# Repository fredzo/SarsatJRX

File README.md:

# Sarsat JRX
Cospas/Sarsat 406MHz beacon decoder based on an ESP32 module.
This project was inspired by the work of F4GMU and F1LVT.

Field use during a SATER exerciser with Ardrasec 31 :

# Hardware
Input stage is based on F1LVT's "deriv-audio" board : http://www.f1lvt.com/files/346-DerivAudio-P3.90.pdf

Second stage is F1LVT's signal shaping stage from DECTRA decoder : http://www.f1lvt.com/files/333E-ConstructionDECTRA2274-P1-English.67.pdf

Audio signal can be provided by either the audio ouput of a receiver (in my case a FT3D portable) or from a NiceRF SA818-S UHF module.

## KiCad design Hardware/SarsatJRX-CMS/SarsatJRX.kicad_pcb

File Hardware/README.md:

# Hardware

The board used is an LilyGo LilyPi : https://opencircuit.fr/produit/lilygo-lily-pi-esp32-wifi-bluetooth-3.5-inch
Based on an ESP32-Wrover-E module from Espressif.

Input stage is based on F1LVT's "deriv-audio" board : http://www.f1lvt.com/files/346-DerivAudio-P3.90.pdf
Second stage is F1LVT's signal shaping stage from DECTRA decoder : http://www.f1lvt.com/files/333E-ConstructionDECTRA2274-P1-English.67.pdf

Audio signal can be provided by either the audio ouput of a receiver or from a NiceRF SA818-S UHF module.

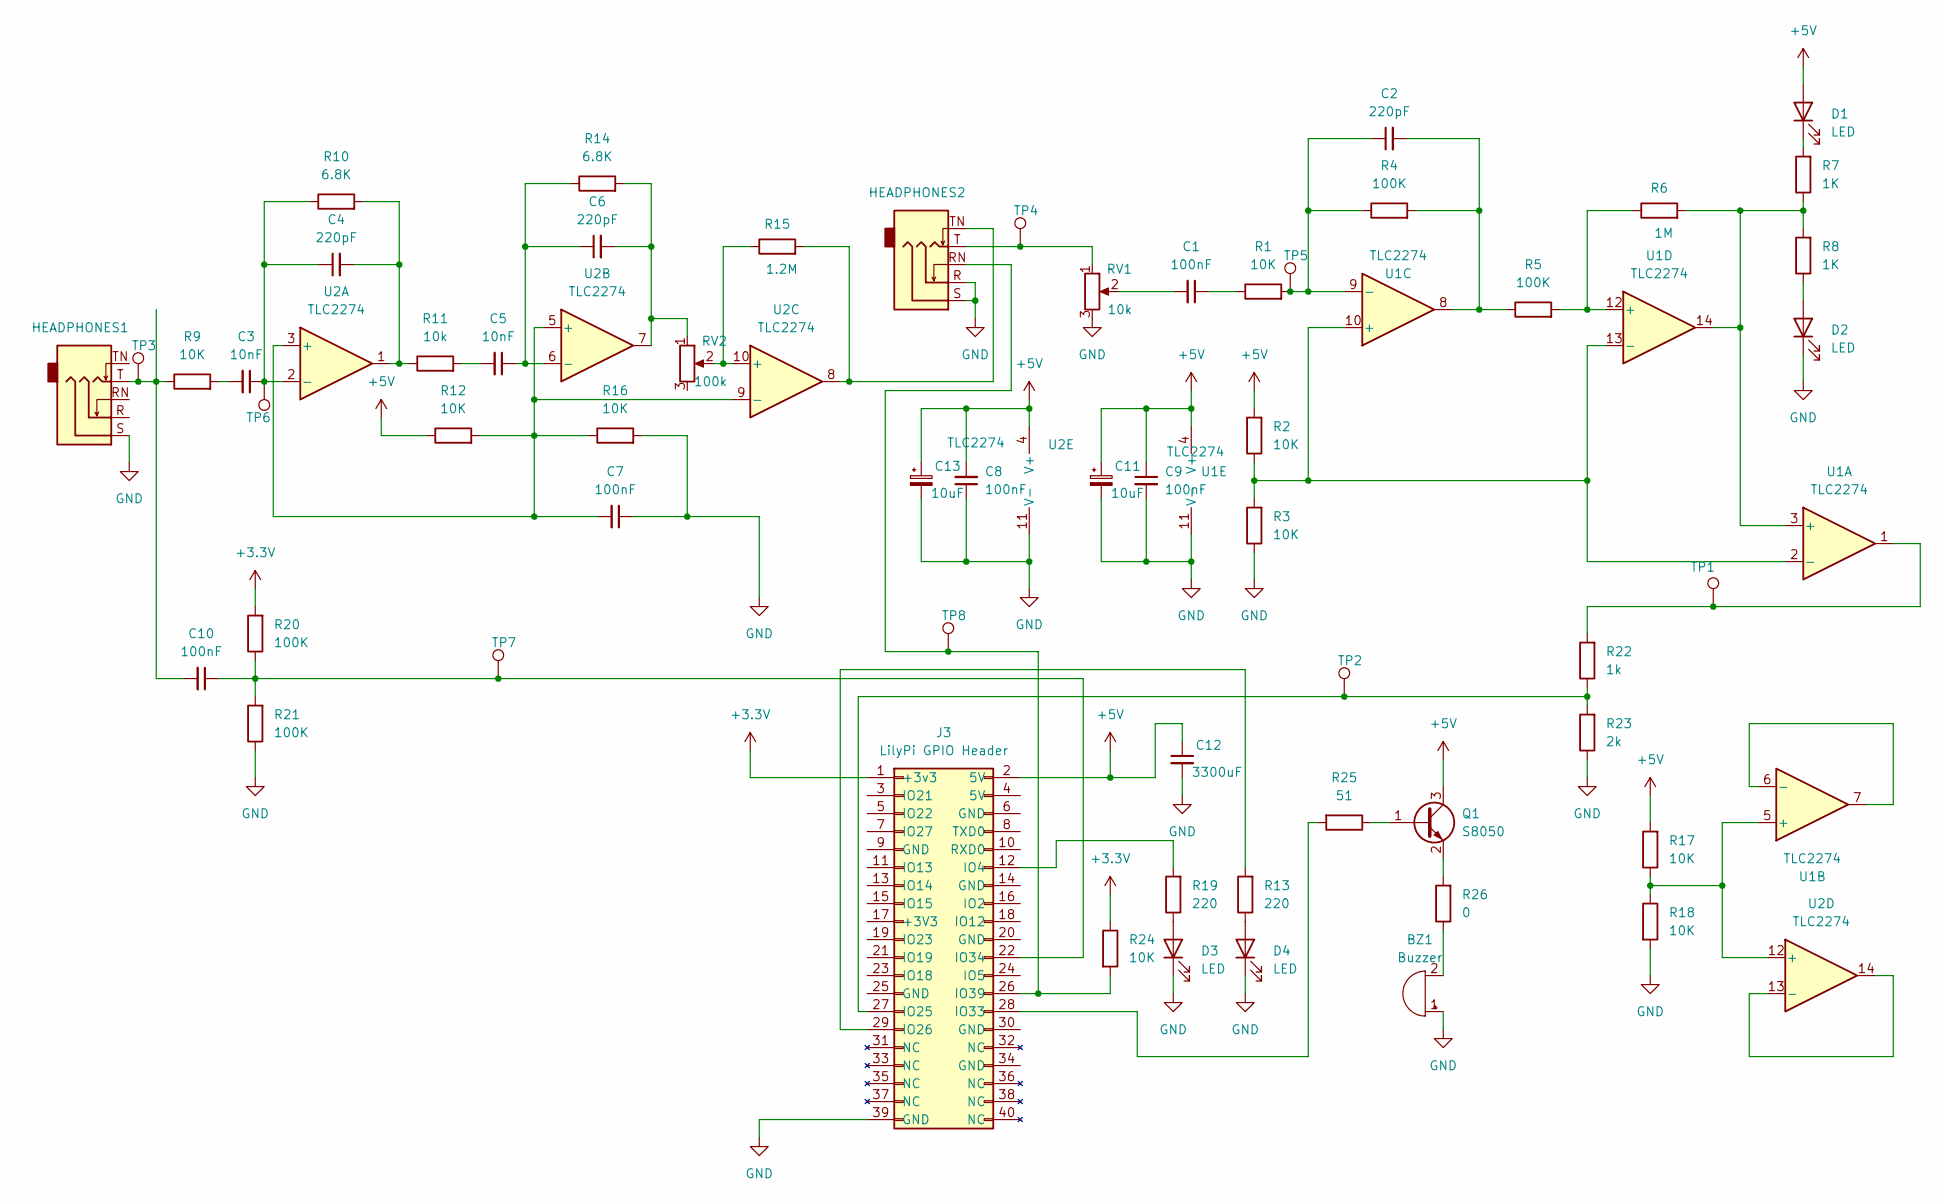
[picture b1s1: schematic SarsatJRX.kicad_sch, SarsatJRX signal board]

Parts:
BZ1: Buzzer; MagneticBuzzer_PUI_AT-0927-TT-6-R-side-horn
C1, C7, C8, C9, C10: 100nF; C_0603_1608Metric
C2, C4, C6: 220pF; C_0603_1608Metric
C3, C5: 10nF; C_0603_1608Metric
C11, C13: 10uF; CP_EIA-3216-18_Kemet-A
C12: 3300uF; CP_Radial_D8.0mm_P3.50mm
D1, D2, D3, D4: LED; LED_D5.0mm
HEADPHONES1, HEADPHONES2: AudioJack3_SwitchTR; PJ-307
J3: LilyPi GPIO Header; RPI_Hat_B+
Q1: S8050; SOT-23-3_L3.0-W1.7-P0.95-LS2.9-BR
R1, R2, R3, R9, R12, R16, R17, R18, R24: 10K; R_0603_1608Metric
R4, R5, R20, R21: 100K; R_0603_1608Metric
R6: 1M; R_0603_1608Metric
R7, R8: 1K; R_0603_1608Metric
R10, R14: 6.8K; R_0603_1608Metric
R11: 10k; R_0603_1608Metric
R13, R19: 220; R_0603_1608Metric
R15: 1.2M; R_0603_1608Metric
R22: 1k; R_0603_1608Metric
R23: 2k; R_0603_1608Metric
R25: 51; R_0603_1608Metric
R26: 0; R_0603_1608Metric
RV1: 10k; Potentiometer_Bourns_3296W_Vertical
RV2: 100k; Potentiometer_Bourns_3296W_Vertical
TP1, TP2, TP3, TP4, TP5, TP6, TP7, TP8: TestPoint_Pad_D1.0mm
U1, U2: TLC2274; SOIC-14_3.9x8.7mm_P1.27mm

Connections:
+3.3V: J3.1 (+3v3), R20.2, R24.1
+5V: C8.2, C9.1, C11.1, C12.1, C13.1, D1.2 (A), J3.2 (5V), Q1.3 (C), R2.2, R12.1, R17.2, U1.4 (V+), U2.4 (V+)
GND: BZ1.1 (+), C7.1, C8.1, C9.2, C11.2, C12.2, C13.2, D2.1 (K), D3.1 (K), D4.1 (K), HEADPHONES1.S, HEADPHONES2.R, HEADPHONES2.S, J3.39 (GND), R3.1, R16.2, R18.2, R21.1, R23.1, RV1.3, U1.11 (V-), U2.11 (V-)
unnamed: BZ1.2 (-), R26.1
unnamed: C1.1, R1.1
unnamed: C1.2, RV1.2
unnamed: C2.2, R4.2, R5.1, U1.8
unnamed: C3.2, R9.2
unnamed: C4.2, R10.2, R11.1, U2.1
unnamed: C5.2, R11.2
unnamed: C6.2, R14.2, RV2.1, U2.7
unnamed: C10.2, HEADPHONES1.T, R9.1, TP3.1
unnamed: D1.1 (K), R7.2
unnamed: D2.2 (A), R8.1
unnamed: D3.2 (A), R19.1
unnamed: D4.2 (A), R13.1
unnamed: HEADPHONES2.T, RV1.1, TP4.1
unnamed: HEADPHONES2.TN, R15.2, U2.8
unnamed: J3.12 (IO4), R19.2
unnamed: J3.27 (IO25), R22.1, R23.2, TP2.1
unnamed: J3.29 (IO26), R13.2
unnamed: J3.28 (IO33), R25.2
unnamed: C10.1, J3.22 (IO34), R20.1, R21.2, TP7.1
unnamed: HEADPHONES2.RN, J3.26 (IO39), R24.2, TP8.1
unnamed: Q1.1 (B), R25.1
unnamed: Q1.2 (E), R26.2
unnamed: R22.2, TP1.1, U1.1
unnamed: R6.2, R7.1, R8.2, U1.3 (+), U1.14
unnamed: R2.1, R3.2, U1.2 (-), U1.10 (+), U1.13 (-)
unnamed: R17.1, R18.1, U1.5 (+), U2.12 (+)
unnamed: U1.6 (-), U1.7
unnamed: C2.1, R1.2, R4.1, TP5.1, U1.9 (-)
unnamed: R5.2, R6.1, U1.12 (+)
unnamed: C7.2, R12.2, R16.1, U2.3 (+), U2.5 (+), U2.9 (-)
unnamed: C3.1, C4.1, R10.1, TP6.1, U2.2 (-)
unnamed: C5.1, C6.1, R14.1, U2.6 (-)
unnamed: R15.1, RV2.2, U2.10 (+)
unnamed: U2.13 (-), U2.14

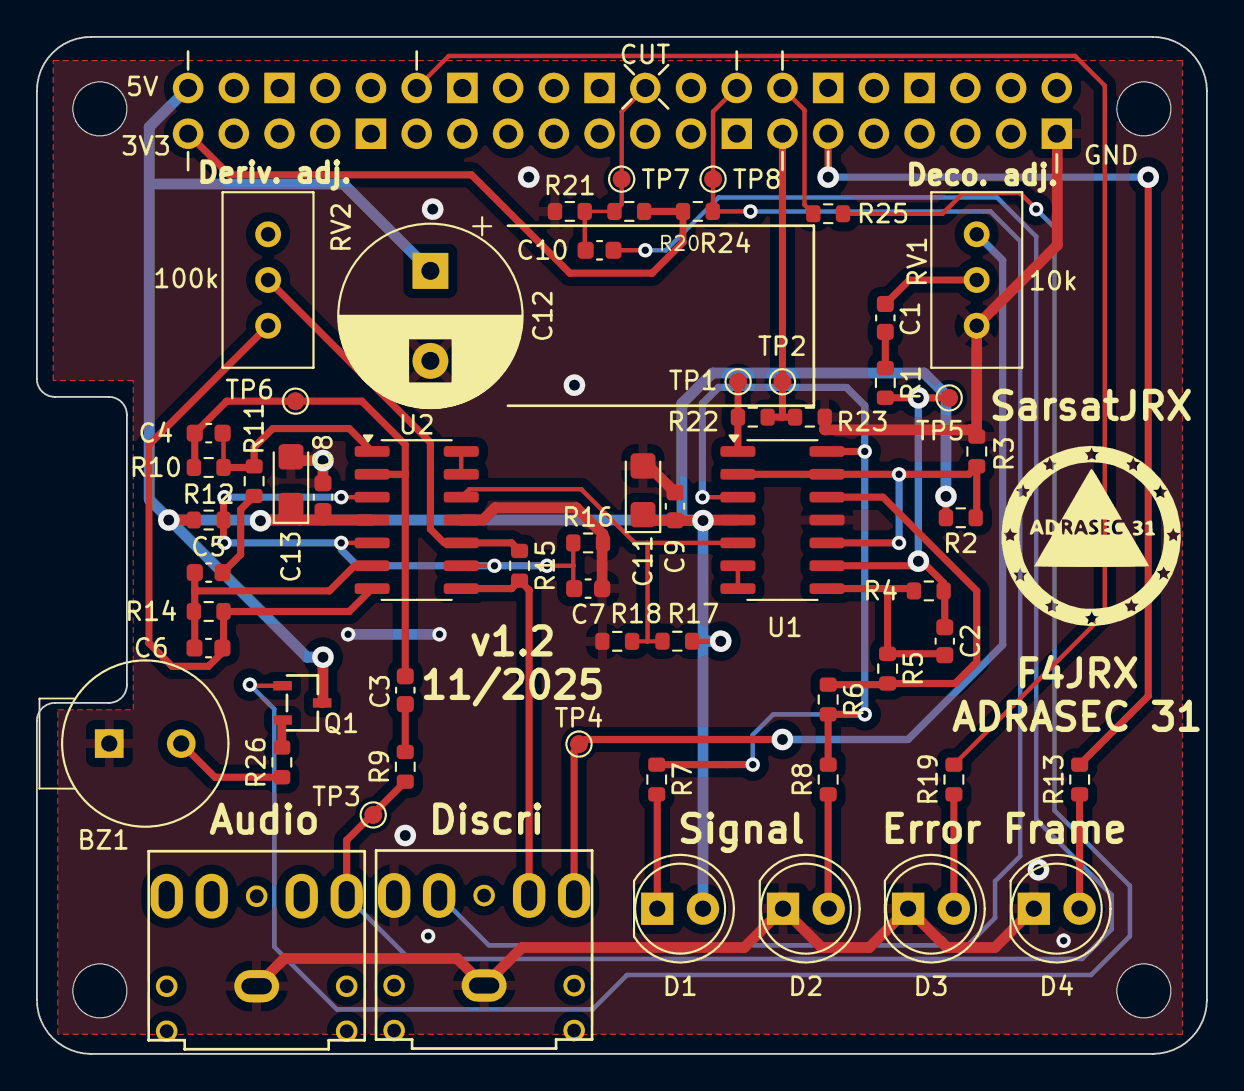
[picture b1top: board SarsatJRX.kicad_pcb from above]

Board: 2 copper layers, 65.0 x 56.5 mm, 60 parts (0 on the bottom side), 38 nets.

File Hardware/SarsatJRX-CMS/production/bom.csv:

Designator,Footprint,Quantity,Value,LCSC Part #
BZ1,MagneticBuzzer_PUI_AT-0927-TT-6-R-side-horn,1,Buzzer,
"C1, C10, C7, C8, C9",0603,5,100nF,
C11,CP_EIA-3216-18_Kemet-A,1,10uF,
C12,CP_Radial_D8.0mm_P3.50mm,1,470uF,
"C2, C4, C6",0603,3,220pF,
"C3, C5",0603,2,10nF,
"D1, D2, D3, D4",LED_D5.0mm,4,LED,
"HEADPHONES1, HEADPHONES2",PJ-307,2,AudioJack3_SwitchTR,
J3,RPI_Hat_B+,1,LilyPi GPIO Header,
Q1,SOT-23-3_L3.0-W1.7-P0.95-LS2.9-BR,1,S8050,
"R1, R11, R12, R16, R17, R18, R2, R24, R3, R9",0603,10,10K,
"R10, R14",0603,2,6.8K,
"R13, R19",0603,2,220,
R15,0603,1,1.2M,
"R20, R21, R4, R5",0603,4,100K,
"R22, R7, R8",0603,3,1k,
R23,0603,1,2k,
R25,0603,1,51,
R26,0603,1,0,
R6,0603,1,1M,
RV1,Potentiometer_Bourns_3296W_Vertical,1,10k,
RV2,Potentiometer_Bourns_3296W_Vertical,1,200k,
"TP1, TP2, TP3, TP4, TP5, TP6, TP7, TP8",TestPoint_Pad_D1.0mm,8,~,
"U1, U2",SOIC-14_3.9x8.7mm_P1.27mm,2,TLC2274,

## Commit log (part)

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2023-08-28 Moved to u8g2 fonts.
2023-08-28 Moved to XPT2046 touch driver (+ added touch calibration mode).
2023-08-29 Added additionnal data, serial number and loacting devices parsing and display.
2023-08-29 Fixed additional data
2023-08-29 LVGL will have to wait for ESP32 board !...
2023-08-30 Fixed screen refresh
2023-08-31 Fixed header display/update
2023-09-01 Added RTC driver
2023-09-01 Added backlight + first step to RTC
2023-09-01 Try and solve I2c communication problem with touch controller
2023-09-02 Esp32 with Arduino GFX Driver => color problem...
2023-09-02 Fixed typo
2023-09-03 Try and move to TFT_eSPI
2023-09-03 Finally fixed TFT_eSPI with official latest version
2023-09-04 Fixed display and touch management.
2023-09-05 Added RTC + time display
2023-09-06 First step to LVGL
2023-09-07 Fixed lvgl conf access
2023-09-07 Added lvgl QR code test
2023-09-08 First step to beacon display with tabview
2023-09-09 Added pagination
2023-09-09 Added proper monospace font
2023-09-09 Fixed some styles, added beacon receive date/time
2023-09-09 Code reorganization / split into several files
2023-09-10 More cleanup + smaller footer.
2023-09-10 Fixed positions
2023-09-10 Fixed bg color for better readability
2023-09-11 Fixed c_str() dangling pointers
2023-09-11 Removed unused features/fonts.
2023-09-11 Fixed led blinking.
2023-09-13 Added wifi provisionning via AutoConf
2023-09-13 Added wifi status indicator
2023-09-13 Added some wifi connection logs
2023-09-13 Fixed RSSI change threshold
2023-09-14 Fixed status management
2023-09-14 Added RTC sync via NTP
2023-09-15 Added favicon.
2023-09-15 Fixed logo + SD Card pins
2023-09-15 Fixed logo position
2023-09-16 Added card remove detection on file write error.
2023-09-16 Fixed some width
2023-09-16 Fixed power display
2023-09-17 Added sketch information.
2023-09-17 Fixed settings positions
2023-09-18 Added network tab (empty for now...)
2023-09-20 Added dBm formatting
2023-09-21 First step to settings saving and Wifi on/off state
2023-09-22 Going on with wifi settings.
2023-09-22 Fixed wifi status
2023-09-22 Network tab
2023-09-23 Fixed wifi tab spacing
2023-09-23 Added OK / KO colors
2023-09-24 Added status to net tab + ok/ko color on wifi and ntp state
2023-09-25 Added mount/unmoint callbacks on sd card toggle
2023-09-25 Going on with sd tab
2023-09-25 Fixed beacon list display
2023-09-25 Prefent wifi rssi change to redraw sd tab
2023-09-27 Changed beacon buttons to iindividual buttons + added a create image button method
2023-09-27 Fixed beacons list navigation
2023-09-27 Added disk beacon date management.
2023-09-27 Added delete beacon on long press
2023-09-27 Added delete on short click with confirm box.
2023-09-27 Remeber last beacon index + fixed beacon select after deleting last item.
2023-09-28 Bumped dra818 submodule
2023-09-28 Moved all PIN declarations to SarsatJRX conf file + first step to DRA818 lib use.
2023-09-29 DRA818 module bump
2023-10-03 Fixed Simu init
2023-10-03 Added version command
2023-10-03 First step to power metter.
2023-10-03 Fixed meter positionning.
2023-10-04 Fixed read_group
2023-10-04 Switched to async mode for dra module
2023-10-04 Scan mode
2023-10-04 Fixed stop scan
2023-10-06 Fixed scan button behaviour
2023-10-09 Added LCD font
2023-10-09 Updated radio display
2023-10-10 Added radio on/off settings management
2023-10-11 Added radio meter
2023-10-12 Finaly found a working keyboard implementation.... Lvgl v8.3.9 (same with 8.3.10) as a bug that makes the whole keyboard re-render on each keystroke. A working solution has been found but needs to re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
2023-10-12 Fixed freq edit auto-content
2023-10-12 Fxied autocoretion + added prev/next freq actions
2023-10-12 Added radio version
2023-10-12 Added filter and volume settings.
2023-10-12 Fixed radio init.
2023-10-12 Restored settings after radio start.
2023-10-13 Fixed compilation error
2023-10-13 Added volume spinbox
2023-10-13 Split of UiSettings file
2023-10-13 First step to frequency list
2023-10-13 Fixed frequ list order and size
2023-10-14 Added frequencies tick/untick
2023-10-15 Better frequency formating + added radion frequency list config
2023-10-15 Fixed frequency item formatting. Fixed frequency increment.
2023-10-15 Added freq list edit
2023-10-31 Added volatile and IRAM_ATTR flags for variable and methods used in ISR.
2024-04-11 Added TODOs
2024-04-12 First step to audio tab addition Added squelch to radio tab and moved volume to audio tab Added Set squelch to radio
2024-04-12 Removed unused defines
2024-04-12 Added squelch value ui update.
2024-04-13 Fixed radioVolume ui update
2024-04-13 Added deleteAllBeacons from filesystem method
2024-04-13 Fixed async mode Fixed ret code values
2024-04-13 Reduced beacon list size to reduce memory issues Fixed radio calls (only rssi and scan are async + call filters after group command to set them back
2024-04-13 Fixed power meter range
2025-05-08 Removed radio stuff. First step to audio input measurement. First step to new PCB.
2025-05-31 First step to case extender.
2025-05-31 Added top cuttings
2025-06-01 Fist step tp top
2025-06-01 FInished top front holes !
2025-06-01 Added top filet.
2025-06-02 Finihed top anchors
2025-06-02 Fixed transformation names.
2025-06-02 Added mesh versions
2025-06-03 Added printing holders
2025-07-26 Rmoved printing holders
2025-07-26 Enlarged top
2025-07-27 Fixed realigning holes
2025-07-27 Fixed switch hole
2025-07-27 Fixed hole shape
2025-07-29 First step to new inputs and ouptus (error led, buzzer, disci jack, charge etc.).
2025-07-29 Moved power functions in a dedicated class
2025-07-31 Fixed power module (flickering led state detection + optimization of adc sampling logic). Some ui refactoring.
2025-08-01 Big ui refactoring. Moved ui update logic to Display class and have it called from lvgl task.
2025-08-01 Added in frame led error handling.
2025-08-01 Fixed error led logic.
2025-08-02 Added rolling average for power measurment. Added parametrable min and max values for battery voltage. Fixed battery icon width.
2025-08-02 Fixed battery indicator.
2025-08-02 First step to adding buzzer.
2025-08-03 Updated lvgl version.
2025-08-03 Fixed footer display logic
2025-08-03 Fixed delete beacon logic. Added sound on frame receive.
2025-08-04 Added discri jack handling in header / footer (hide audio metter).
2025-08-04 Chaged audio adc to IO39 and disci jack detection input to IO34 (since IO39 does not support internal pull-up).
2025-08-04 Restored pin assignement since IO34 needs external pull-up too anyway...
2025-08-04 Fixed footer style for frame notif.
2025-08-04 Added touch sound.
2025-08-04 Added new settings.
2025-08-04 Fixed settings.
2025-08-05 Added screen saver management.
2025-08-05 Updateed display settings screen with latest settings..
2025-08-05 Added audio settings
2025-08-06 Added allow frame simulation settings. Fixed screen saver dialog. Fixed ':' formatting. Fixed buzzer level spinbox
2025-08-06 Fixed screen saver logic.
2025-08-06 Added settings to show battery warn message. Added Turn Off button on display settings. Fixed buzzer level spinbox font.
2025-08-06 Tried to solve full vs on battery iatus.
2025-08-06 Added charging led indicators.
2025-08-06 Fixed full notif led.
2025-08-07 Removed unused line.
2025-08-08 Fixed calendar display
2025-08-08 Only show battery dialog once.
2025-08-11 Added test points.
2025-08-11 Fixed snprintf calls when used buffer is not locally declared.
2025-08-11 Fixed some silkscreen
2025-08-11 Fixed screen saver by blacking the display. Added screen on on usb power deconnection.
2025-08-11 Hardware v1.1 production files.
2025-08-11 Fixed screen on logic.
2025-08-14 Added isFrameValid() method.
2025-08-27 Fixed rear side opening positions (USB/Relay).
2025-08-27 Fixed barrel jack position
2025-08-27 Added buzzer hole.
2025-09-01 Fixed beacon screen after simu or sd read when in settings.
2025-09-03 Added utime and vbat raw value to system screen
2025-09-04 Added red led + sound + countdown restart on invalid frame reception. Fixed reload countdown time. Removed use of RTC int timer (not working, probably hardware problem) and replaced with ESP32 hardwa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
2025-09-05 Fixed invalid frame sound init
2025-09-05 Added new additional symbols
2025-09-05 Fixed new symbols. Moved settings tab header to icons.
2025-09-05 Fixed sd card access speed.
2025-09-05 First step to settings reorganization
2025-09-06 Added new radio icon for frame settings. Cleaned-up audio settings tab. Added filter settings.
2025-09-07 Fixed battery detection.
2025-09-08 Fixed frame filter logic and sound.
2025-09-09 Added preferences to sd card.
2025-09-10 Only restart countdown on non filtered frames, or invalid frames, but close to countdown end.
2025-09-10 Prevent auto-reload countdown when overlapping.
2025-09-10 Fixed main tab icons.
2025-09-10 Fixed QR display when location is not available.
2025-09-11 Added wifi ssid and password to Settings + removed Autoconnect wifi credential backup + made AP mode default.
2025-09-11 Fixed buzzer hole position
2025-09-11 Fixed DC jack position.
2025-09-11 Fixed case
2025-09-11 Fixed wifi blik anim.
2025-09-12 Fixed NTP sync when current RTC year is > 2016.
2025-09-12 Fixed ntp.
2025-09-14 Added timeZone to settings. Fixed NTP sync.
2025-09-15 Added handling of conrner cases (empty frame etc.) in beacon parsing.
2025-09-16 Removed Autoconnect Portal. Moved to AsyncWebServer.
2025-09-16 Added mDNS to resolve sarsatjrx.local
2025-09-17 Added wifi config ssid/psk. Removed network tab and merged it to wifi tab. Moved to v1.0.0.
2025-09-17 Update ntp state on ntp sync event. Fixed battery state display.
2025-09-20 Fixed frame name (title) depending on protocol type.
2025-09-22 First step to SSE
2025-09-28 Added cors headers. Fixed sse event fromat.
2025-09-29 Added toKvpString() method for beacon serialization. Some refactoring.
2025-09-30 Fixed CORS headers.
2025-10-01 Fixed DC hole jack size.
2025-10-01 Fixed 3.5 jack holes size (changed diameter from 7mm to 6.4mm).
2025-10-01 New case version (small adjustements on buzzer hole, DC jack and audio jack holes)
2025-10-02 Fixed led header display. Frame and error led stay on for 2 seconds rather than 1.
2025-10-05 Remvoved location from Orbitography frames. Added battery percentage and sd card status to tick events. Fixed Locator display.
2025-10-06 Fixed frame annouce on wifi.
2025-10-14 Firest step to adding qr code for app connection
2025-10-14 Moved app qr code to param tab with audio.
2025-10-14 Added reset countdown endpoint + changed reset behaviour to start countdown when paused and pause it when started.
2025-10-15 Moved buzzer hole 0.5mm right.
2025-10-15 Fixed insertion holes.
2025-10-15 Added wifi ssid/pass 1 and 2
2025-10-15 Added support for 3 different wifi ssid/pass connection options.
2025-10-24 Added settings to WifiManager. Fixed DNS display.
2025-10-24 First step to config update via App.
2025-10-25 Going on with config update with app.
2025-10-26 Fixed auto-save duration. Prevent from exiting settings screen on app reconnection.
2025-10-26 Fixed post config.
2025-10-27 Fixed HTTP return code. Removed workstation mode. Moved buzzer sound to main loop core.
2025-10-30 Fixed BL on boot.
2025-10-30 Added string setting saving right.
2025-10-31 Fixed 5V line capacitor value (3300uF) + footprint. Added decoupling capacitor to U2 power line. Added RV1/2 value sikl screen. Added slik screen to mark connector pins that have to be soldered. Move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
2025-11-04 Add initial documentation for SarsatJRX Beacon Decoder
2025-11-04 Moved to v1.0.1
2025-11-07 Added crowdin actions
2025-11-07 no message
2025-11-07 Change file type from 'fm_markdown' to 'markdown'
2025-11-07 Reformat Crowdin upload workflow YAML
2025-11-07 Modify translation path in Crowdin upload workflow
    Updated the translation path in the Crowdin upload workflow.
2025-11-07 Update Crowdin download workflow to target markdown files
2025-11-07 Update translation file naming in workflow
2025-12-17 Added screenshot endpoint.
2026-05-21 Fixed serial number calculation.
